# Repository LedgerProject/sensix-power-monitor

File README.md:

## SPD Enclosure based PowerMonitor - 2 DIN Modules - Single/Three Phase

## Table of contents

* [Built with](#built-with)
* [Software used](#dependencies)
* [Directory structure](#directory-structure)
* [Flash instructions](#flash-instructions)
* [Running tests](#running-tests)
* [Hardware Design](#hardware-design)

## Built with 

* [ESP-IDF](https://www.espressif.com/en/products/sdks/esp-idf)

## Software used 

* [ESP-IDF Toolchain](https://www.espressif.com/en/products/sdks/esp-idf)
* [CMake](https://cmake.org/download/)
* [Arduino ADE9153a](https://github.com/analogdevicesinc/arduino/tree/master/Arduino%20Uno%20R3/libraries/ADE9153A)
* [minfft](https://github.com/aimukhin/minfft)
* [fmtlib](https://github.com/fmtlib/fmt)
* [Microsoft GSL](https://github.com/microsoft/GSL)

## Directory structure 

* `3rdparty`: Third party code and dependencies
* `cmake`: Additional CMake scripts used to configure and build the project
* `data`: Resources embedded in the final binary
* `hardware_design`: Hardware design files
* `main`: ESP IDF component
* `src`: Source code
* `src/include`: Header files
* `test`: Unit tests (meant to be run on PC)

## Flash instructions 

After setting up the ESP IDF build environment and making sure the tools are available in your PATH, run:

```
idf.py build # Build the source code
idf.py -p <port> flash
idf.py -p <port> monitor
```

## Running tests 

Make sure you have CMake and CTest available in your PATH and a C and C++ compiler available.

Run:

```
mkdir build && cd build
cmake .. && cmake --build .
ctest
```

## Hardware Design 

Design files for PowerMonitor hardware for development:

* SPD_PowerMonitor-AFE - board containing the analog frontend and isolation barrier
* SPD_PowerMonitor-Controller - board containing the ESP32 MCU with RS485 and USB for software debugging

Characteristics:

* Designed to fit into a 2 DIN Module SPD base enclosure
* Instead of Ethernet and 24V AC power the controller has a USB transciever chip to ease development
* Powered by USB 5V DC
* Breakout headers for internal SPI bus in order to experiment with external RAM
* Breakout headers for I2C bus to add ST NFC module for configuration loading
* Shunt mounted directly on the SPD spade plugs

**Notes**

From software side this is the final design, any changes to hardware should be transparent to software. On hardware
side, because of chip shortages and especially the low availability of the isolated power supply for the AFE, this
design will have to be modified to use other ICs that are available. Analog FE will not change.

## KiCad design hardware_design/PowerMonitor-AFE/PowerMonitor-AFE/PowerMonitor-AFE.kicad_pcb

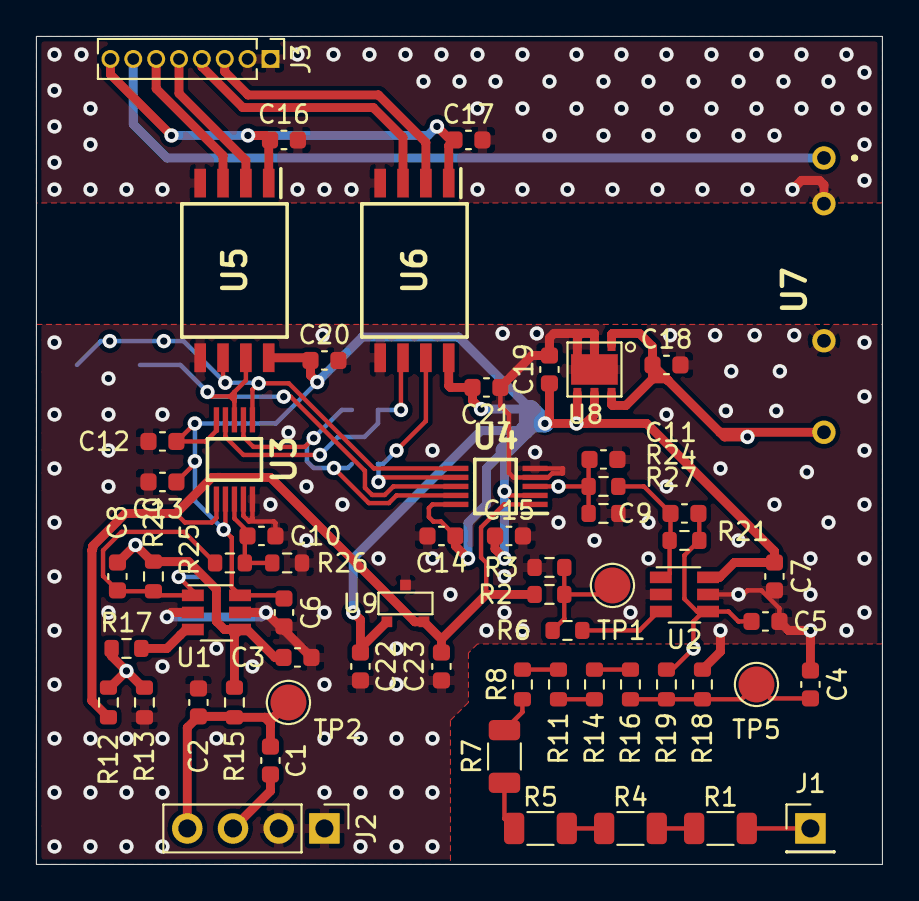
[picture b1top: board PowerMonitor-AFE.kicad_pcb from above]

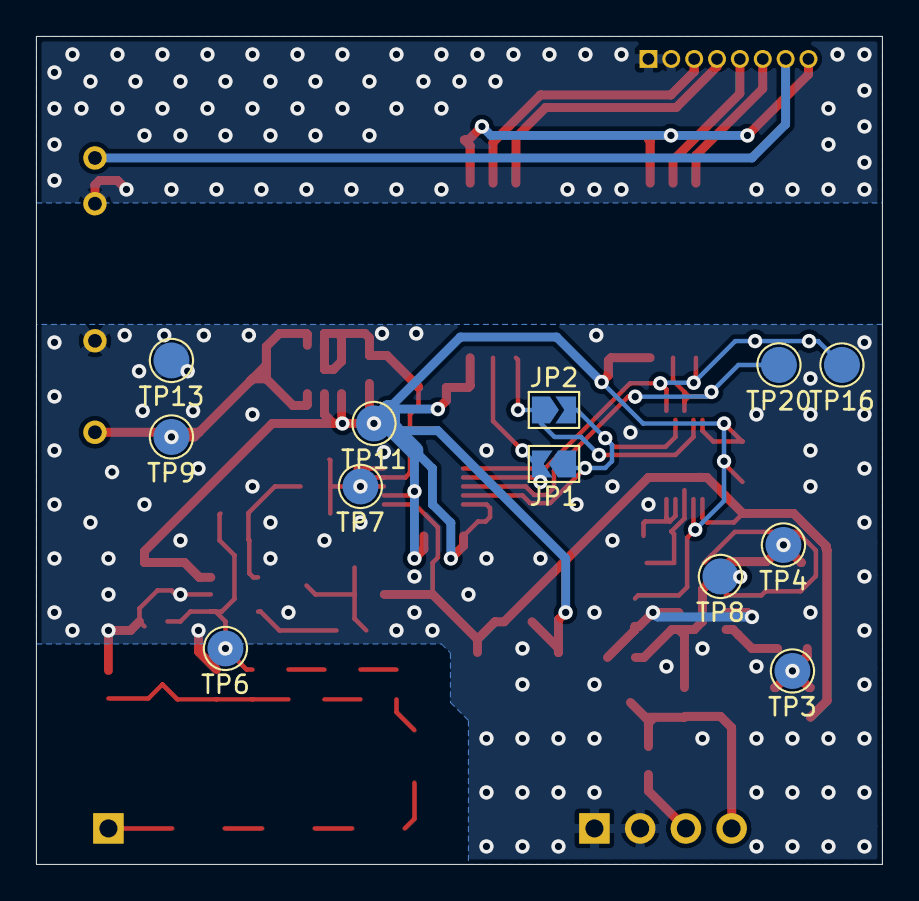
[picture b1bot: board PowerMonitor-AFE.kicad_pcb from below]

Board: 2 copper layers, 47.0 x 46.0 mm, 73 parts (12 on the bottom side), 37 nets.

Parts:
C1, C3, C5, C8, C9, C10, C11: DNP; C_0603_1608Metric
C2, C4: 1n; C_0603_1608Metric
C6, C7, C12, C13, C14, C15, C16, C17, C20, C21, C22: 0.1u; C_0603_1608Metric
C18, C19, C23: 1u; C_0603_1608Metric
J1: Conn_01x01; PinHeader_1x01_P2.54mm_Vertical
J2: Conn_01x04; PinHeader_1x04_P2.54mm_Vertical
J3: Conn_01x08; PinHeader_1x08_P1.27mm_Vertical
JP1, JP2: SolderJumper_2_Open; SolderJumper-2_P1.3mm_Open_TrianglePad1.0x1.5mm
R1, R4, R5, R7: 249k; R_1206_3216Metric
R2, R8, R11, R12, R14, R16, R24, R25, R26, R27: 1k; R_0603_1608Metric
R3, R13: 100; R_0603_1608Metric
R6, R17: 0R; R_0603_1608Metric
R15: 100K; R_0603_1608Metric
R18: 330; R_0603_1608Metric
R19: 100k; R_0603_1608Metric
R20, R21: 1M; R_0603_1608Metric
TP1, TP2, TP3, TP4, TP5, TP6, TP7, TP8, TP9, TP11, TP13, TP16, TP20: TestPoint; TestPoint_Pad_D2.0mm
U1, U2: ADA4098-1; TSOT-23-6
U3, U4: ADS8866; SOP50P490X110-10N
U5: MAX22245; SOIC127P1031X265-8N
U6: MAX22246; SOIC127P1031X265-8N
U7: TEA1-0505HI; TEA10505HI
U8: NCP691MN33T2G; DFN6 3x3 0.95
U9: ADR380ARTZ-REEL7; SOT-23

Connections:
+3.3VP: C6.2, C7.2, C12.2, C13.1, C14.2, C15.1, C19.1, C20.1, C21.1, C22.1, TP11.1, U1.6, U2.6, U3.2, U3.10, U4.2, U4.10, U5.8, U6.8, U8.4, U8.5, U9.1
+3V3: C16.1, C17.1, J3.8, U5.1, U6.1
+5V: J3.7, U7.1
+5VP: C18.1, TP9.1, U7.7, U8.1, U8.6
CONVST: TP16.1, U3.6, U4.6, U5.6
CONV_START: J3.6, U5.3
DIN_EXT: JP2.1, U3.9, U6.6
DOUT_A: JP1.1, JP2.2, U3.7, U4.9
DOUT_EXT: JP1.2, U4.7, U6.7
GND1: C16.2, C17.2, J3.1, J3.2, U5.4, U6.4, U7.2
GND2: C2.1, C3.1, C4.1, C5.1, C6.1, C7.1, C10.1, C11.1, C12.1, C13.2, C14.1, C15.2, C18.2, C19.2, C20.2, C21.2, C22.2, C23.2, J2.1, J2.2, R3.1, R13.1, R18.2, R26.2, R27.2, TP13.1, U1.2, U1.5, U2.2, U2.5, U3.4, U3.5, U4.4, U4.5, U5.5, U6.5, U7.5, U8.2, U8.3, U8.EP, U9.3
unnamed: C1.1, C2.2, J2.4, R15.1, TP2.1
unnamed: C1.2, J2.3
unnamed: C3.2, C8.2, R15.2, R20.2, TP4.1, U1.4
unnamed: C4.2, R16.2, R18.1, R19.1, TP5.1
unnamed: C5.2, C9.2, R19.2, R21.2, TP6.1, U2.4
unnamed: C8.1, R20.1, R25.1, TP8.1, U1.1
unnamed: C9.1, R21.1, R24.1, U2.1
unnamed: C10.2, R25.2, R26.1, U3.3
unnamed: C11.2, R24.2, R27.1, TP7.1, U4.3
unnamed: J1.1, R1.1
unnamed: R1.2, R4.1
unnamed: R2.2, R3.2, R6.1, TP1.1
unnamed: R4.2, R5.1
unnamed: R5.2, R7.1
unnamed: R6.2, U2.3
unnamed: R7.2, R8.1
unnamed: R8.2, R11.1
unnamed: R11.2, R14.1
unnamed: R12.2, R13.2, R17.1, TP3.1
unnamed: R14.2, R16.1
unnamed: R17.2, U1.3
SCLK: TP20.1, U3.8, U4.8, U5.7
SPI_0_CLK: J3.5, U5.2
SPI_0_MISO: J3.3, U6.2
SPI_0_MOSI: J3.4, U6.3
VREF: C23.1, R2.1, R12.1, U3.1, U4.1, U9.2

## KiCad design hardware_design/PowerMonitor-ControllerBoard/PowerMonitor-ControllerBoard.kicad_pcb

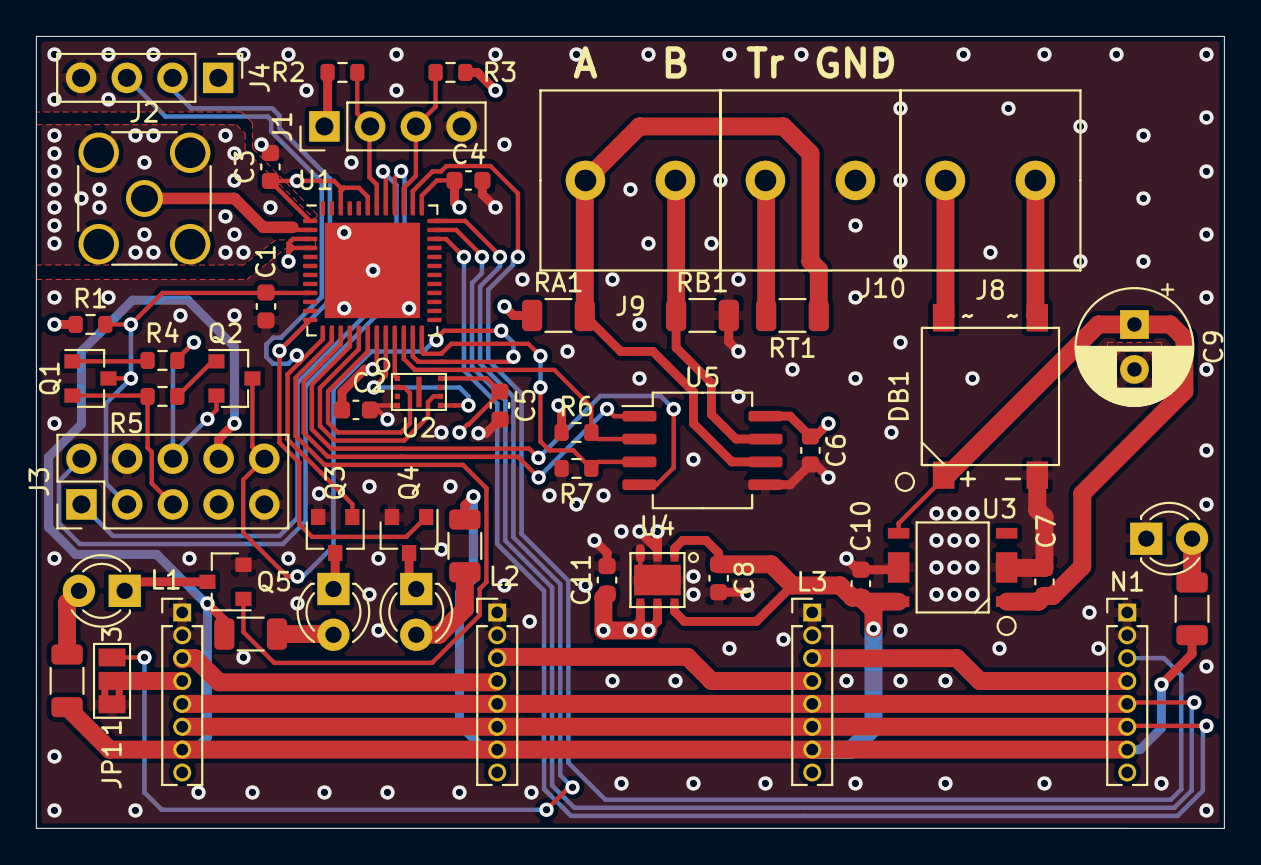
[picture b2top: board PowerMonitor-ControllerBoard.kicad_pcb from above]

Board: 4 copper layers, 66.0 x 44.0 mm, 52 parts (0 on the bottom side), 46 nets.

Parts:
C1, C2, C3, C4, C5, C6, C7, C10: 0.1u; C_0603_1608Metric
C8, C11: 1u; C_0603_1608Metric
C9: 4700u; CP_Radial_D6.3mm_P2.50mm
DB1: DF01S-T
J1: CON_I2C; PinHeader_1x04_P2.54mm_Vertical
J2: Conn_Coaxial; SMA_Wurth_60312002114503_Vertical
J3: Conn_02x05_Counter_Clockwise; PinHeader_2x05_P2.54mm_Vertical
J4: Conn_01x04; PinHeader_1x04_P2.54mm_Vertical
J8, J9, J10: Conn_01x02; 1792863
JP1: DATA_OUT_SEL; SolderJumper-3_P1.3mm_Bridged2Bar12_Pad1.0x1.5mm_NumberLabe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
L1, L2, L3: Conn_01x08; PinHeader_1x08_P1.27mm_Vertical
LED_ACT1: LED; LED_D3.0mm
LED_ALERT_1, LED_ALERT_2: LED; LED_D3.0mm
LED_PWR1: LED; LED_D3.0mm
N1: Conn_01x08; PinHeader_1x08_P1.27mm_Vertical
Q1, Q2, Q3, Q4, Q5: Q_NPN_BEC; SOT-23
R1, R6, R7: 10k; R_0603_1608Metric
R2, R3: 2k2; R_0603_1608Metric
R4, R5: 1k; R_0603_1608Metric
RA1: 1k; R_1206_3216Metric
RB1: 1k; R_1206_3216Metric
RT1: 120; R_1206_3216Metric
R_LED_ACT1: TBD; R_1206_3216Metric
R_LED_ALERT_1, R_LED_ALERT_2: TBD; R_1206_3216Metric
R_LED_PWR1: TBD; R_1206_3216Metric
U1: ESP32-PICO-D4; QFN-48-1EP_7x7mm_P0.5mm_EP5.3x5.3mm
U2: APS1604M-3SQR-ZR; USON-8L 3x2 ZR
U3: R1518S501B-E2-FE; HSOP-6J
U4: NCP691MN33T2G; DFN6 3x3 0.95
U5: MAX3485; SO-8_5.3x6.2mm_P1.27mm

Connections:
+3V3: C2.1, C3.1, C4.1, C5.1, C6.1, C11.1, J1.1, J3.7, J4.1, L1.8, L2.8, L3.8, N1.8, R1.1, R2.1, R3.1, R6.1, RA1.1, U1.1, U1.3, U1.4, U1.19, U1.37, U1.43, U1.46, U2.8, U4.4, U4.5, U5.8
+5V: C8.1, C10.1, J3.8, L1.7, L2.7, L3.7, N1.7, R_LED_ACT1.1, R_LED_ALERT_1.1, R_LED_ALERT_2.1, R_LED_PWR1.1, U3.6, U4.1, U4.6
ACT_LED: Q5.1, U1.14
ALERT_1: J4.2, Q4.1, U1.12
ALERT_2: J4.3, Q3.1, U1.13
BOOT_MODE: J3.10, Q2.3, U1.23
CONV_START: L1.6, L2.6, L3.6, N1.6, U1.34
DE: R7.1, U1.24, U5.3
DTR: J3.6, Q2.2, R4.1
EN: C1.1, J3.3, Q1.3, R1.2, U1.9
GND: C1.2, C2.2, C3.2, C4.2, C5.2, C6.2, C7.2, C8.2, C9.2, C10.2, C11.2, DB1.3, J1.4, J2.2, J3.4, J3.9, J4.4, J10.2, JP1.1, L1.1, L1.2, L2.1, L2.2, L3.1, L3.2, LED_PWR1.1, N1.1, N1.2, Q3.2, Q4.2, Q5.2, R7.2, RB1.2, U1.49, U2.4, U3.2, U3.5, U4.2, U4.3, U4.EP, U5.5
LNA: J2.1, U1.2
unnamed: DB1.2, J8.2
unnamed: DB1.4, J8.1
unnamed: JP1.2, L1.4
unnamed: L1.3, L2.4
unnamed: L2.3, L3.4
unnamed: L3.3, N1.4
unnamed: LED_ACT1.1, Q5.3
unnamed: LED_ACT1.2, R_LED_ACT1.2
unnamed: LED_ALERT_1.1, Q4.3
unnamed: LED_ALERT_1.2, R_LED_ALERT_1.2
unnamed: LED_ALERT_2.1, Q3.3
unnamed: LED_ALERT_2.2, R_LED_ALERT_2.2
unnamed: LED_PWR1.2, R_LED_PWR1.2
unnamed: Q1.1, R4.2
unnamed: Q2.1, R5.2
RE: R6.2, U1.22, U5.2
RS485_A: J9.1, RA1.2, RT1.1, U5.6
RS485_B: J9.2, RB1.1, U5.7
RS485_TR: J10.1, RT1.2
RTS: J3.5, Q1.2, R5.1
RXD0: J3.2, U1.40
RXD1: U1.15, U5.1
SCL: J1.3, R3.2, U1.39
SDA: J1.2, R2.2, U1.42
SPI_0_CLK: L1.5, L2.5, L3.5, N1.5, U1.35
SPI_0_MISO: N1.3, U1.38
SPI_0_MOSI: JP1.3, U1.36
SPI_1_CLK: U1.17, U2.6
SPI_1_CS: U1.21, U2.1
SPI_1_MISO: U1.18, U2.2
SPI_1_MOSI: U1.20, U2.5
TXD0: J3.1, U1.41
TXD1: U1.16, U5.4
VDC: C7.1, C9.1, DB1.1, U3.1, U3.4

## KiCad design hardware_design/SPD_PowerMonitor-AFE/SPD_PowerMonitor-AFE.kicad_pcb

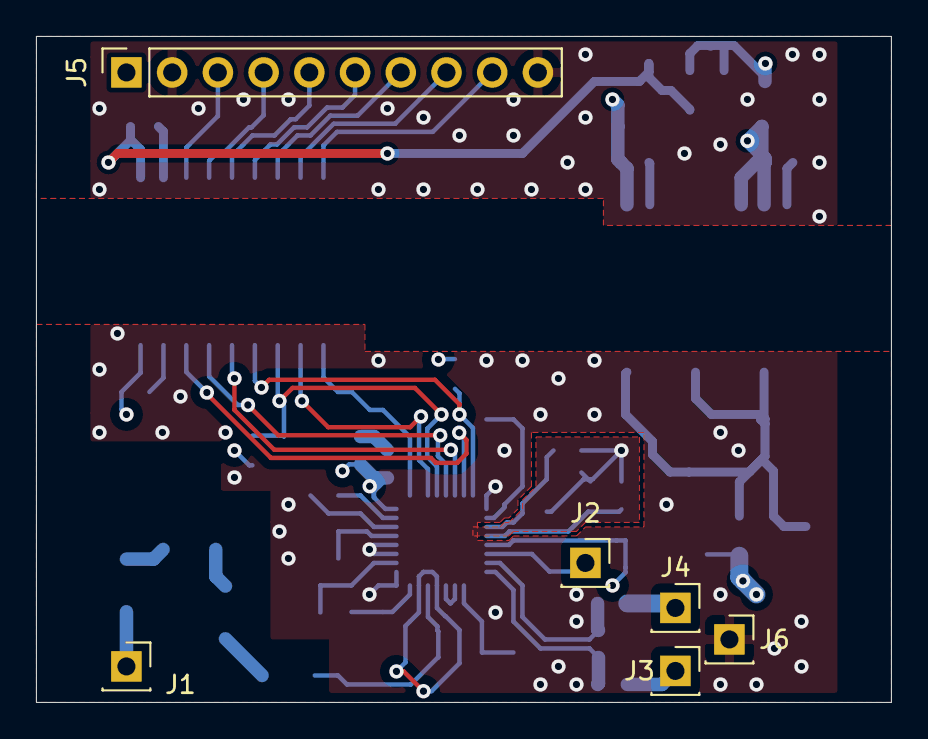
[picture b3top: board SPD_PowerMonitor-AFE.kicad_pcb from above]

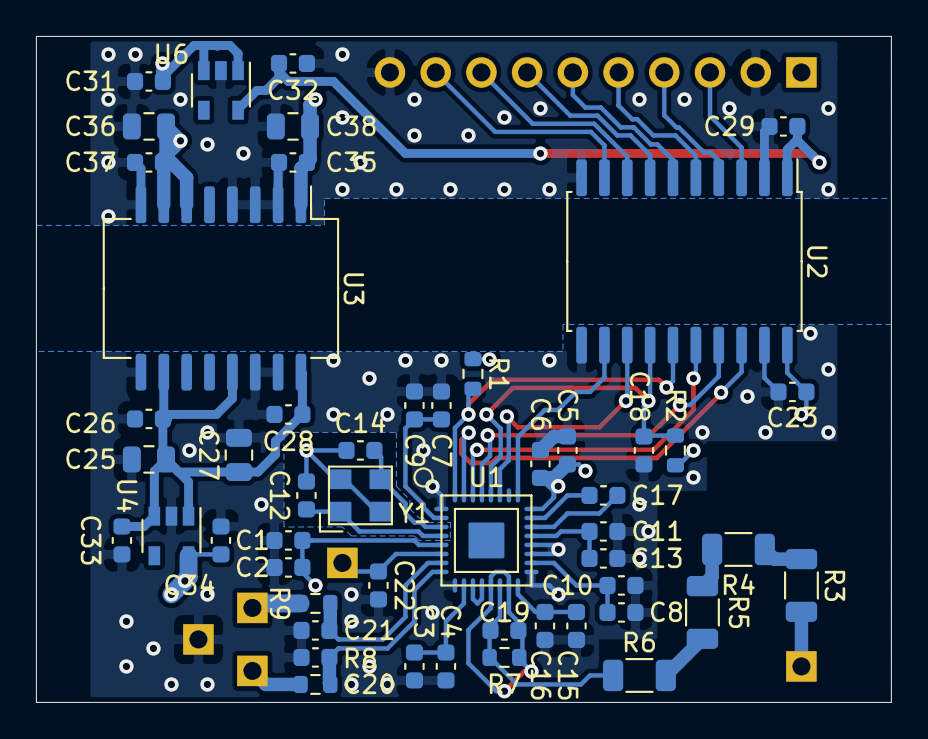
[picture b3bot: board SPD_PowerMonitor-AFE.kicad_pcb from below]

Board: 4 copper layers, 47.5 x 37.0 mm, 57 parts (51 on the bottom side), 41 nets.

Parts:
C1, C3, C5, C7, C8, C15: 4.7uF; C_0603_1608Metric
C2, C4, C6, C9, C10, C13, C16, C20, C21, C22, C23, C26, C28, C29, C35, C37: 0.1uF; C_0603_1608Metric
C11, C17: 0.47uF; C_0603_1608Metric
C12, C14: 12pF; C_0603_1608Metric
C18: 1uF; C_0603_1608Metric
C19: 15nF; C_0603_1608Metric
C25, C27, C36, C38: 10uF; C_0805_2012Metric
C31, C32, C33, C34: C; C_0603_1608Metric
J1, J2, J3, J4, J6: Conn_01x01; PinSocket_1x01_P2.54mm_Vertical
J5: Conn_01x10; PinSocket_1x10_P2.54mm_Vertical
R1, R2: 10k; R_0603_1608Metric
R3, R4, R5, R6: 250k; R_1206_3216Metric
R7: 1k; R_0603_1608Metric
R8, R9: 150k; R_0603_1608Metric
U1: ADE9153A; LFCSP_5_5_0.75_32
U2: ADuM4152BRIZ; SOIC-20W_7.5x12.8mm_P1.27mm
U3: ADuM6000ARIZ; SOIC-16W_7.5x12.8mm_P1.27mm
U4, U6: AP2112K-3.3; SOT-23-5
Y1: 12.288MHz 12pF 20ppm; ECX-33Q

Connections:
AVDDOUT: C15.1, C16.1, U1.16
CF2_LIVE: U1.25, U2.12
CF_2: J5.9, U2.9
CLKIN: C12.1, U1.4, Y1.1
CLKOUT: C14.1, U1.3, Y1.3
DVDDOUT: C7.1, C9.1, U1.2
GND: C1.2, C2.2, C3.2, C4.2, C5.2, C6.2, C7.2, C8.2, C9.2, C10.2, C11.2, C12.2, C13.2, C14.2, C15.2, C16.2, C18.2, C20.2, C21.1, C22.2, C23.2, C25.2, C26.2, C27.2, C28.2, C33.2, C34.2, J6.1, U1.1, U1.9, U1.17, U1.19, U1.20, U2.11, U2.19, U3.9, U3.14, U3.15, U4.2, Y1.2, Y1.4
GNDD: C29.2, C31.2, C32.2, C35.2, C36.2, C37.2, C38.2, J5.2, J5.10, U2.2, U2.10, U3.2, U3.3, U3.4, U3.8, U6.2
IAMS: C22.1, J2.1, U1.6
IAN: C21.2, R9.2, U1.7
IAP: C20.1, R8.2, U1.8
IRQ: J5.8, U2.8
IRQ_LIVE: U1.27, U2.13
LIN: J3.1, R8.1
LOUT: J4.1, R9.1
MISO: J5.5, U2.5
MISO_LIVE: U1.30, U2.16
MOSI: J5.4, U2.4
MOSI_LIVE: U1.29, U2.17
MSH: C11.1, C13.1, U1.21
N: J1.1, R3.2
unnamed: C17.1, U1.23
unnamed: C17.2, U1.22
unnamed: R3.1, R4.2
unnamed: R4.1, R5.2
unnamed: R5.1, R6.2
unnamed: U1.11, U1.12
REFIN: C8.1, C10.1, U1.18
RESET: J5.7, U2.7
RESET_LIVE: C18.1, R2.2, U1.28, U2.14
SCLK: J5.3, U2.3
SCLK_LIVE: U1.31, U2.18
SS: J5.6, U2.6
SS_LIVE: R1.2, U1.32, U2.15
V3V3: C29.1, C32.1, U2.1, U6.5
V3V3_ISO: C1.1, C2.1, C5.1, C6.1, C23.1, C34.1, R1.1, R2.1, U1.5, U1.24, U2.20, U4.5
V5V: C31.1, C35.1, C36.1, C37.1, C38.1, J5.1, U3.1, U3.6, U3.7, U6.1, U6.3
V5V_ISO: C25.1, C26.1, C27.1, C28.1, C33.1, U3.10, U3.13, U3.16, U4.1, U4.3
VAN: C19.2, R7.1, U1.13, U1.15
VAP: C19.1, R6.1, R7.2, U1.14
VDDOUT2P5: C3.1, C4.1, U1.10

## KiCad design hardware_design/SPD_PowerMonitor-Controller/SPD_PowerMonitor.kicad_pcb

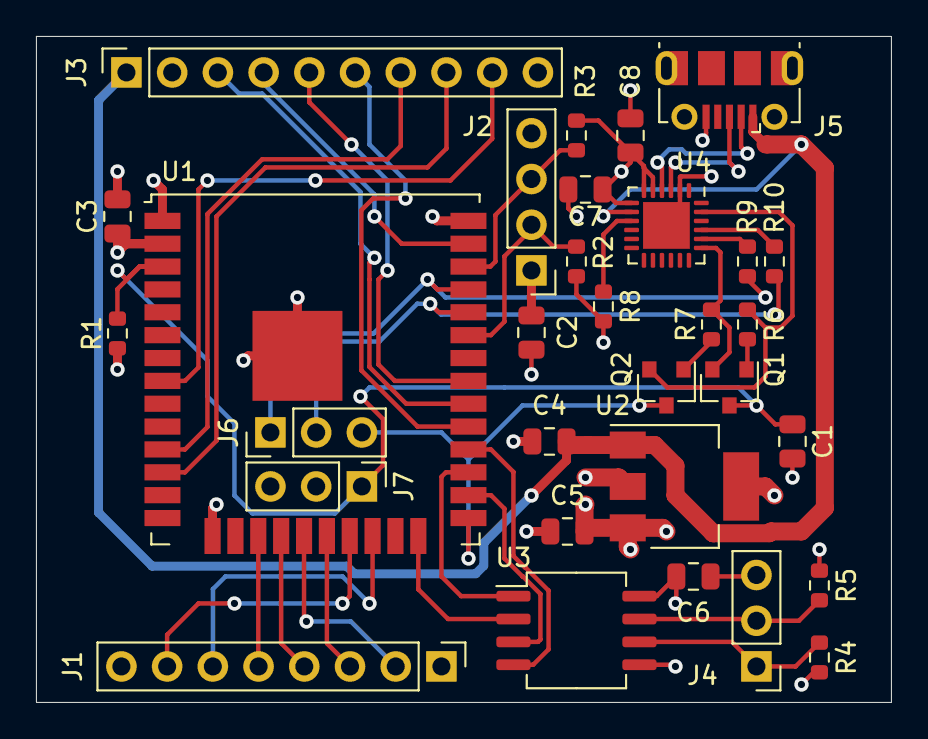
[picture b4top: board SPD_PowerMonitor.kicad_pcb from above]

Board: 4 copper layers, 47.5 x 37.0 mm, 31 parts (0 on the bottom side), 37 nets.

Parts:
C1, C2, C3, C4, C5, C6, C7, C8: C; C_0805_2012Metric
J1: Conn_01x08; PinHeader_1x08_P2.54mm_Vertical
J2: Conn_01x04; PinHeader_1x04_P2.54mm_Vertical
J3: Conn_01x10; PinSocket_1x10_P2.54mm_Vertical
J4, J6, J7: Conn_01x03; PinHeader_1x03_P2.54mm_Vertical
J5: USB_B_Micro; USB_Micro-B_Molex-105017-0001
Q1, Q2: Q_NPN_BEC; SOT-23
R1, R2, R3, R4, R5, R6, R7, R8, R9, R10: R; R_0603_1608Metric
U1: ESP32-WROOM-32U
U2: TC1262-33; SOT-223-3_TabPin2
U3: MAX3485; SO-8_5.3x6.2mm_P1.27mm
U4: CP2102N-A01-GQFN24; QFN-24-1EP_4x4mm_P0.5mm_EP2.6x2.6mm

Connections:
+3V3: C2.1, C3.1, C5.1, C6.1, C7.1, C8.1, J1.8, J2.1, R1.1, R2.1, R3.1, R4.1, R8.1, U1.2, U2.3, U3.8, U4.5, U4.6, U4.7
+5V: C4.1, J3.1, J5.1, U2.1, U4.8
BOOT_MODE: J6.3, Q2.3, U1.25
CF2_ADE: J3.9, U1.8
DE: U1.26, U3.3
DTR: Q2.2, R6.2, U4.23
EN: C1.1, J7.1, Q1.3, R1.2, U1.3
GND: C1.2, C2.2, C3.2, C4.2, C5.2, C6.2, C7.2, C8.2, J1.1, J2.4, J3.2, J3.10, J4.3, J5.5, J7.2, J7.3, R5.2, U1.1, U1.15, U1.38, U1.39, U2.2, U3.5, U4.2, U4.25
IRQ_ADE: J3.8, U1.12
unnamed: J1.2, U1.19
unnamed: J1.3, U1.20
unnamed: J1.4, U1.18
unnamed: J1.5, U1.17
unnamed: J1.6, U1.22
unnamed: J1.7, U1.21
unnamed: J4.1, R4.2, U3.6
unnamed: J4.2, R5.1, U3.7
unnamed: J5.2, U4.4
unnamed: J5.3, U4.3
unnamed: Q1.1, R6.1
unnamed: Q2.1, R7.1
unnamed: R8.2, U4.9
unnamed: R9.2, U4.20
unnamed: R10.2, U4.21
RE: U1.24, U3.2
RESET_ADE: J3.7, U1.11
RTS: Q1.2, R7.2, U4.19
RXD0: J6.2, R10.1, U1.34
RXD2: U1.27, U3.1
SCL: J2.3, R3.2, U1.36
SDA: J2.2, R2.2, U1.33
SPI_CLK: J3.3, U1.30
SPI_CS_0: J3.6, U1.29
SPI_MISO: J3.5, U1.31
SPI_MOSI: J3.4, U1.37
TXD0: J6.1, R9.1, U1.35
TXD2: U1.28, U3.4

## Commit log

2021-11-21 PowerMonitor firmware and hardware design - in one huge commit
